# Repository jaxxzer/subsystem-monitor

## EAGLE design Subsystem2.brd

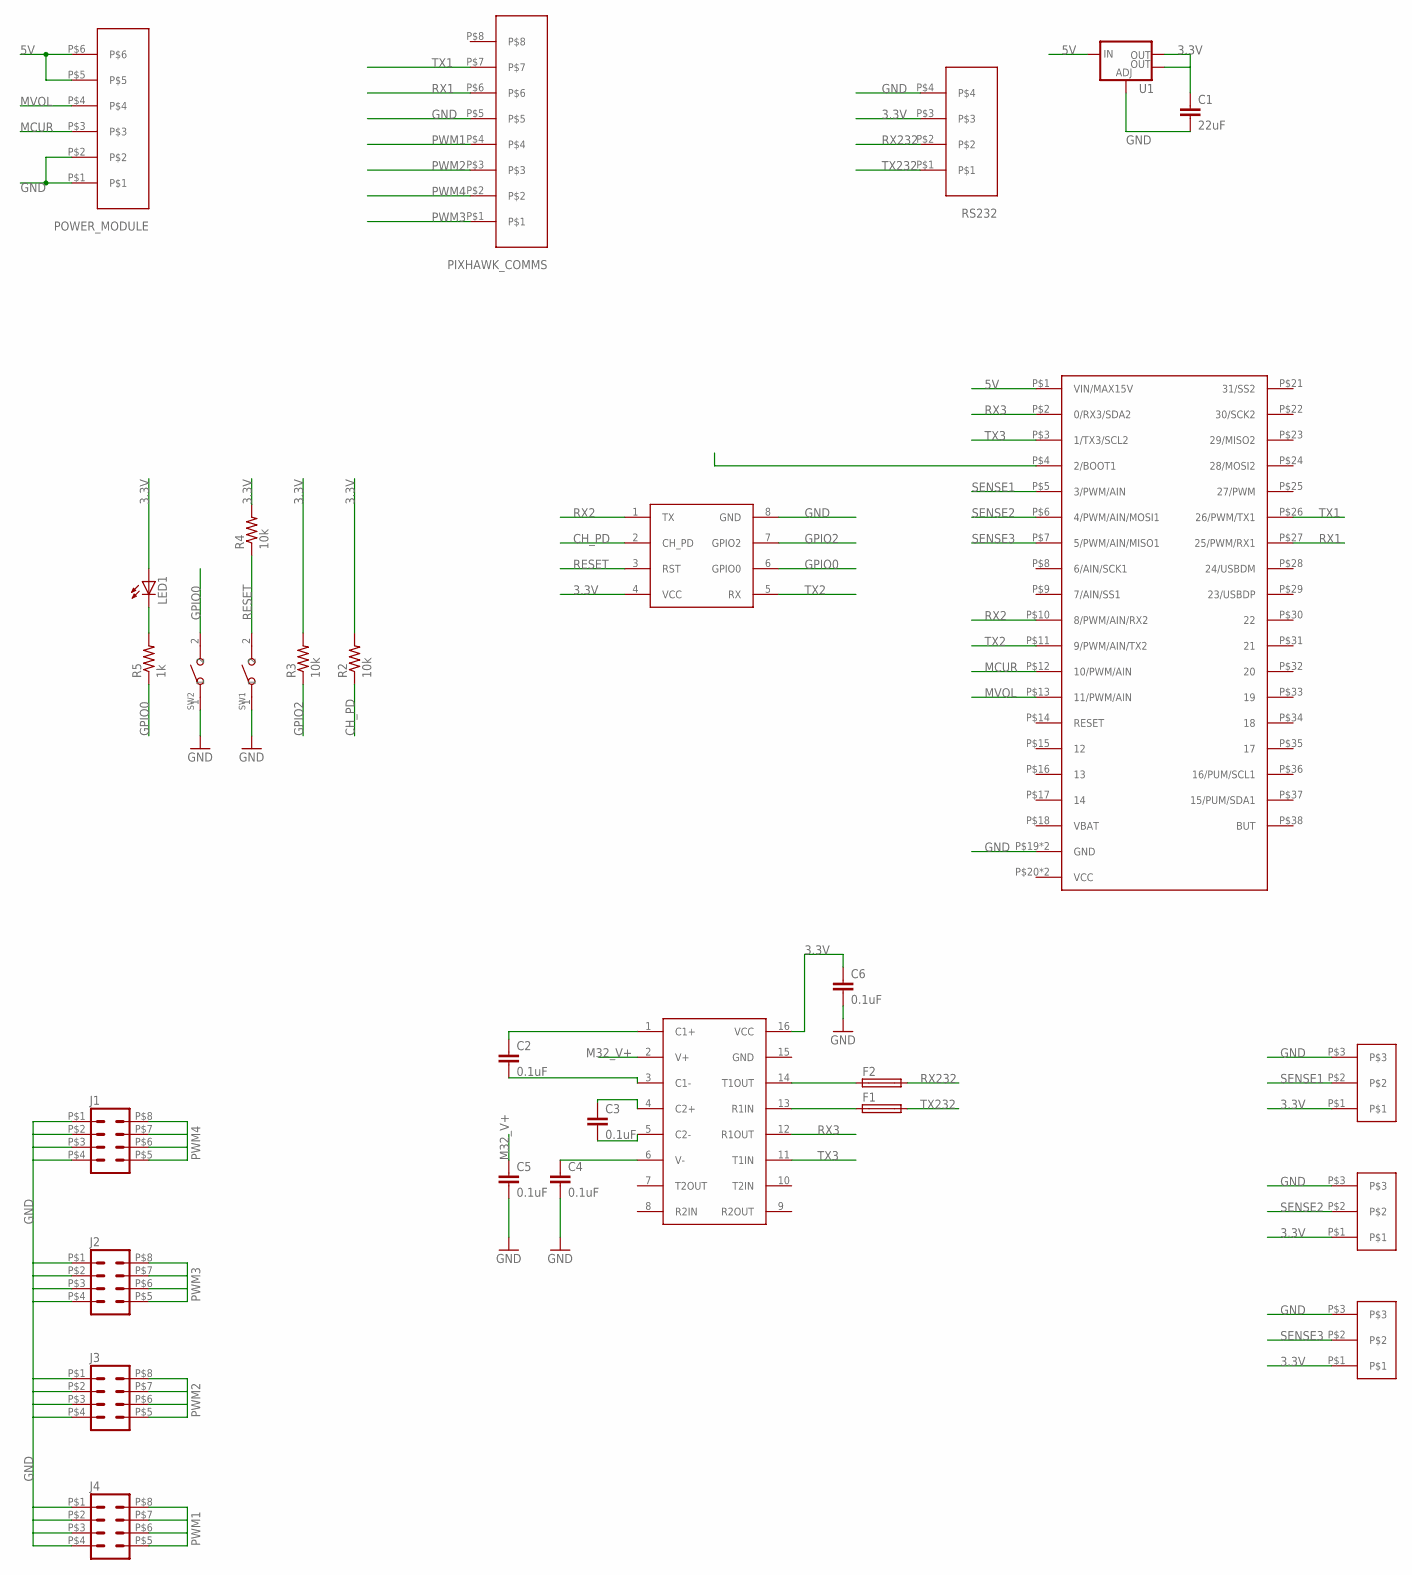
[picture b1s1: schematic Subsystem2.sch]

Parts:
C1: 22uF; 0805
C2, C3, C4, C5, C6: 0.1uF; 0805
F1, F2: TE5
J1, J2, J3, J4: M04X2; 2X4
LED1: LED1206; LED-1206
PIXHAWK_COMMS: 8PIN-PLUG
POWER_MODULE: 6PIN-PLUG
R2, R3, R4: 10k; 0805
R5: 1k; 0805
RS232: 4PIN-PLUG
SW1, SW2: SMD-BUTTON(2P-6.0X3.0X2.5MM)-DHT-1163S; SW2-4.0-6.0X3.0X2.5MM
U1: V_REG_LM1117SOT223; SOT223
U$1: MAPLE-MINI-SOCKET
U$2: MAX3232
U$3: ESP-01
U$4, U$5, U$6: 3PIN-PLUG

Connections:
3.3V: C1.1, C6.1, LED1.A, R2.2, R3.2, R4.2, RS232.P$3, U1.2 (OUT), U1.4 (OUT), U$2.16 (VCC), U$3.4 (VCC), U$4.P$1, U$5.P$1, U$6.P$1
5V: POWER_MODULE.P$5, POWER_MODULE.P$6, U1.3 (IN), U$1.P$1 (VIN/MAX15V)
CH_PD: R2.1, U$3.2 (CH_PD)
GND: C1.2, C4.2, C5.2, C6.2, J1.P$1 (1), J1.P$2 (2), J1.P$3 (3), J1.P$4 (4), J2.P$1 (1), J2.P$2 (2), J2.P$3 (3), J2.P$4 (4), J3.P$1 (1), J3.P$2 (2), J3.P$3 (3), J3.P$4 (4), J4.P$1 (1), J4.P$2 (2), J4.P$3 (3), J4.P$4 (4), PIXHAWK_COMMS.P$5, POWER_MODULE.P$1, POWER_MODULE.P$2, RS232.P$4, SW1.1, SW2.1, U1.1 (ADJ), U$1.P$19 (GND), U$1.P$39 (GND), U$3.8 (GND), U$4.P$3, U$5.P$3, U$6.P$3
GPIO0: R5.1, SW2.2, U$3.6 (GPIO0)
GPIO2: R3.1, U$3.7 (GPIO2)
M32_C1+: C2.1, U$2.1 (C1+)
M32_C1-: C2.2, U$2.3 (C1-)
M32_C2+: C3.1, U$2.4 (C2+)
M32_C2-: C3.2, U$2.5 (C2-)
M32_V+: C5.1, U$2.2 (V+)
M32_V-: C4.1, U$2.6 (V-)
MCUR: POWER_MODULE.P$3, U$1.P$12 (10/PWM/AIN)
MVOL: POWER_MODULE.P$4, U$1.P$13 (11/PWM/AIN)
unnamed: F2.1, U$2.14 (T1OUT)
unnamed: F1.1, U$2.13 (R1IN)
unnamed: LED1.C, R5.2
PWM1: J4.P$5 (5), J4.P$6 (6), J4.P$7 (7), J4.P$8 (8), PIXHAWK_COMMS.P$4
PWM2: J3.P$5 (5), J3.P$6 (6), J3.P$7 (7), J3.P$8 (8), PIXHAWK_COMMS.P$3
PWM3: J2.P$5 (5), J2.P$6 (6), J2.P$7 (7), J2.P$8 (8), PIXHAWK_COMMS.P$1
PWM4: J1.P$5 (5), J1.P$6 (6), J1.P$7 (7), J1.P$8 (8), PIXHAWK_COMMS.P$2
RESET: R4.1, SW1.2, U$3.3 (RST)
RX1: PIXHAWK_COMMS.P$6, U$1.P$27 (25/PWM/RX1)
RX2: U$1.P$10 (8/PWM/AIN/RX2), U$3.1 (TX)
RX3: U$1.P$2 (0/RX3/SDA2), U$2.12 (R1OUT)
RX232: F2.2, RS232.P$2
SENSE1: U$1.P$5 (3/PWM/AIN), U$4.P$2
SENSE2: U$1.P$6 (4/PWM/AIN/MOSI1), U$5.P$2
SENSE3: U$1.P$7 (5/PWM/AIN/MISO1), U$6.P$2
TX1: PIXHAWK_COMMS.P$7, U$1.P$26 (26/PWM/TX1)
TX2: U$1.P$11 (9/PWM/AIN/TX2), U$3.5 (RX)
TX3: U$1.P$3 (1/TX3/SCL2), U$2.11 (T1IN)
TX232: F1.2, RS232.P$1

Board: 2 copper layers, 29 parts (0 on the bottom side), 33 nets, no tracks yet.

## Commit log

2016-07-25 Schematic V1
2016-08-16 Schematic V2\n Check for errors
2016-08-17 add .gitignore
2016-08-17 V2 new board
2016-08-17 add 3232 external caps
2016-08-17 finish first-draft schematic of v2 board

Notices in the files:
parts and their libraries:
SparkFun-Aesthetics: Licensing: Creative Commons ShareAlike 4.0 International - https://creativecommons.org/licenses/by-sa/4.0
